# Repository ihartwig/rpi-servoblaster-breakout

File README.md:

# rpi-servoblaster-breakout

[Order from DirtyPCB now!](http://dirtypcbs.com/view.php?share=18349&accesskey=)

Servo breakout for RPi 0/1/2 based on the [servoblaster](https://github.com/richardghirst/PiBits/tree/master/ServoBlaster)/pi-blaster software. This board supports the default location of 8 servos. In most cases it passively wires the servos to the right pins with shared power and ground rails. A level shifter can be added if your servos require a logic pulse above the RPi's 3.3V. The board is small to reduce cost and fit on both Pi 1 and Pi 0.

You'll need a stacking female 2x13 header to connect to the RPi, commonly found at [Adafruit](https://www.adafruit.com/products/1112) or [Toby Electronics](http://www.toby.co.uk/content/catalogue/products.aspx?series=REF-18xxxx-0x). This header can be soldered directly to the board or fed into a [bottom-entry SMT header](http://www.toby.co.uk/content/catalogue/products.aspx?series=REF-1826xx-0x) soldered onto the top.

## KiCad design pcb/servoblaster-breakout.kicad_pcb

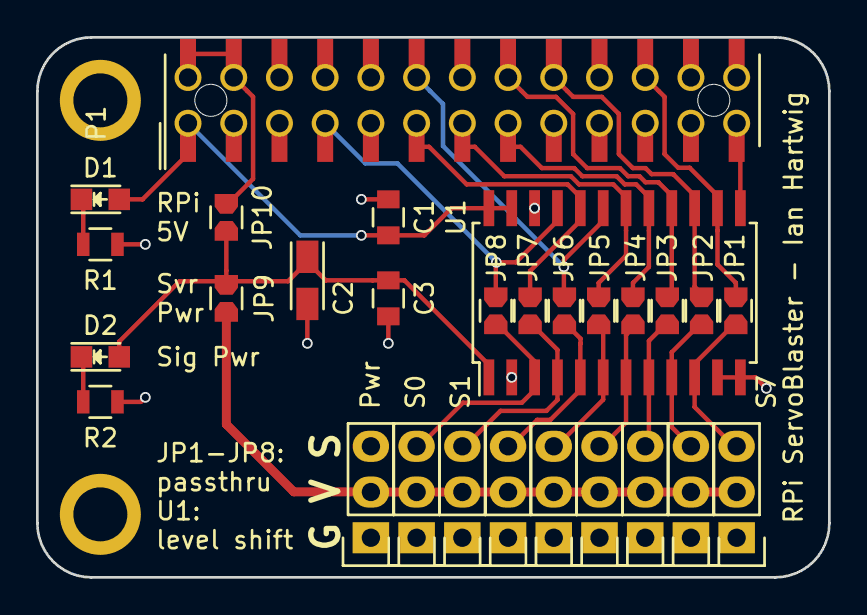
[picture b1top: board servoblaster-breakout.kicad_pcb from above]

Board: 2 copper layers, 44.0 x 30.0 mm, 30 parts (0 on the bottom side), 23 nets.

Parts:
C1, C3: 0.1uF; C_0805
C2: 4.7uF; TantalC_SizeA_EIA-3216_Reflow
D1, D2: S Pwr; LED-0805
H1, H2: hole-grounded-no4; hole-no4
JP1, JP2, JP3, JP4, JP5, JP6, JP7, JP8, JP9, JP10: Jumper_NO_Small; SB_0805
P1: CONN_02X13; Pin_Header_Straight_TH-SMT_2x13
P2, P3, P4, P5, P6, P7, P8, P9, P10: CONN_01X03; Pin_Header_Straight_1x03
R1, R2: 220; R_0805
U1: 74LVC4245A; SOIC-24_7.5x15.4mm_Pitch1.27mm

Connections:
/GPIO4_TDI: JP8.1, P1.7, U1.21
/GPIO17: JP7.1, P1.11, U1.20
/GPIO18: JP6.1, P1.12, U1.19
/GPIO22_TRST: JP4.1, P1.15, U1.17
/GPIO23_RTCK: JP3.1, P1.16, U1.16
/GPIO24_TDO: JP2.1, P1.18, U1.15
/GPIO25_TCK: JP1.1, P1.22, U1.14
/GPIO27_TMS: JP5.1, P1.13, U1.18
/RPI_3V3_1: C1.1, D1.2, P1.1, U1.23, U1.24
/RPI_VBUS: JP10.2, P1.2, P1.4
/SERVO0: JP8.2, P3.3, U1.3
/SERVO1: JP7.2, P4.3, U1.4
/SERVO2: JP6.2, P5.3, U1.5
/SERVO3: JP5.2, P6.3, U1.6
/SERVO4: JP4.2, P7.3, U1.7
/SERVO5: JP3.2, P8.3, U1.8
/SERVO6: JP2.2, P9.3, U1.9
/SERVO7: JP1.2, P10.3, U1.10
GND: C1.2, C2.2, C3.2, P1.6, P1.9, P1.14, P1.20, P1.25, P2.1, P3.1, P4.1, P5.1, P6.1, P7.1, P8.1, P9.1, P10.1, R1.2, R2.2, U1.2, U1.11, U1.12, U1.13, U1.22
unnamed: C2.1, C3.1, D2.2, JP9.1, JP10.1, U1.1
unnamed: D1.1, R1.1
unnamed: D2.1, R2.1
VCC: JP9.2, P2.2, P3.2, P4.2, P5.2, P6.2, P7.2, P8.2, P9.2, P10.2

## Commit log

2016-03-17 rev 1 board layout
2016-03-17 add render to readme
2016-03-22 rename repo and board directory
2016-03-22 fix readme image
2016-03-22 update solder bridge part to not have paste
